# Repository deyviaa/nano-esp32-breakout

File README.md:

# 🛠️ ArdNanoESP32 DevBoard

> *A compact, feature-packed carrier board for the Arduino Nano ESP32 — bridging the gap between bare breadboard chaos and a polished development kit.*

---

## 📖 Overview

This project is a custom-designed **PCB carrier board** built around the **Arduino Nano ESP32** (dual-core Xtensa LX7, Wi-Fi + BLE). Sized to an approximate **iPhone footprint**, the board is designed as an intermediate prototyping platform with a philosophy of **hardware-level safety** ("student-proofing") — all peripherals are wired with protection resistors, clean logic states, and deliberate design choices baked in at the schematic level.

The board seats the Nano ESP32 in ZIF-style socket headers and exposes every GPIO to parallel jumper pin headers for external breadboard connectivity, while also integrating a full suite of on-board peripherals ready for immediate use.

**Current Status:**

```
✅ Schematic design — Complete & verified
✅ Component footprints — All assigned & resolved
✅ Git version control — Initialized (cross-platform)
🔄 PCB Layout & Routing — In Progress
⬜ Gerber Generation & Fab — Pending
⬜ Assembly & Bring-up — Pending
```

---

## ⚡ Power Architecture

The board runs two accessible power rails sourced from the Nano ESP32's onboard regulators:

| Rail | Source | Purpose |
|------|--------|---------|
| **5V** | `VUSB` | WS2812B LED, raw power header |
| **3.3V** | Nano onboard LDO | All logic peripherals, GPIO I/O, I2C bus |
| **GND** | Common ground | Shared reference for all rails |

All power rails are broken out to dedicated 4-pin headers on the board edge for external use.

---

## 🧩 Peripheral Map

```
┌─────────────────────────────────────────────────────────┐
│               Arduino Nano ESP32 Carrier Board           │
│                                                         │
│  ┌──────────────┐     ┌─────────────┐                   │
│  │ Nano ESP32   │     │  4x LEDs    │ ── 1kΩ CLR ── GPIO │
│  │  (socketed)  │     │  4x Buttons │ ── 10kΩ PD ── GPIO │
│  └──────────────┘     │  4x Switches│ ── 1kΩ SER ── GPIO │
│                        └─────────────┘                   │
│  ┌──────────────┐     ┌─────────────┐                   │
│  │  WS2812B     │     │  Qwiic/     │                   │
│  │  RGB LED     │     │  STEMMA QT  │ ── SDA(A4)/SCL(A5) │
│  │  (5V + 470Ω) │     │  JST-SH 4P  │ ── 4.7kΩ pull-ups  │
│  └──────────────┘     └─────────────┘                   │
│  ┌──────────────┐     ┌─────────────┐                   │
│  │  Alps RK09K  │     │  12mm Piezo │                   │
│  │  Rotary Pot  │     │  Buzzer     │ ── SW mute ── GPIO  │
│  │  (VDiv/A0)   │     │  (220Ω buf) │                   │
│  └──────────────┘     └─────────────┘                   │
└─────────────────────────────────────────────────────────┘
```

---

## 🔌 Peripheral Specifications

### 💡 LEDs × 4
- Generic standard LEDs, **active-high**
- **1kΩ** current-limiting resistors in series
- Clean GPIO drive, no floating states

### 🔘 Push Buttons × 4
- Momentary tactile switches
- **10kΩ pull-down** resistors → guaranteed `LOW` at rest
- No debounce hardware (handle in firmware or use `INPUT_PULLUP`)

### 🎚️ Slide Switches × 4 (Stateful GPIO Inputs)
- **SS12D00G-G3** SPDT Slide Switches (2.54mm pitch)
- Hard-wired: Pin 1 → 3.3V, Pin 3 → GND, Pin 2 → MCU
- **1kΩ series resistor** between common and GPIO — prevents a dead short if pin is accidentally configured as `OUTPUT LOW`
- ⚠️ *Avoid routing these to ESP32 strapping pins (GPIO0, GPIO3, GPIO45, GPIO46)*

### 🌈 WS2812B Addressable RGB LED
- **5050** form factor, driven from **VUSB (5V)** rail
- **100nF decoupling cap** placed physically adjacent to VDD/GND
- Data driven by 3.3V GPIO through **470Ω series resistor** (signal protection + level tolerance)
- `DOUT` left unconnected — ready for future LED chain expansion

### 🔁 Qwiic / STEMMA QT Connector (I2C)
- **JST-SH SM04B-SRSS-TB**, 1.0mm pitch, 4-pin
- Industry-standard pinout: `GND | 3V3 | SDA | SCL`
- Routed to hardware I2C: **SDA → A4**, **SCL → A5**
- **Two 4.7kΩ pull-up resistors** on SDA and SCL to 3.3V (open-drain compliant)
- Compatible with the entire Sparkfun/Adafruit Qwiic/STEMMA QT ecosystem

### 🎛️ Rotary Potentiometer
- **Alps RK09K** 9mm single-gang
- Wired as a safe voltage divider: Pin 1 → 3.3V, Pin 3 → GND, Wiper → Analog GPIO (A0–A7)
- Footprint includes 2 mechanical snap-in anchor pads for PCB stability

### 🔊 Piezo Buzzer
- **12mm PCB-mount** piezo, standard 7.62mm through-hole pitch
- **220Ω buffer resistor** on signal line
- **Hardware mute switch** (SS12D00 SPDT): one throw connects signal → buzzer positive; mute position leaves the throw floating (no drain-to-GND waste)

---

## 🗂️ Schematic Hierarchy

The project uses a hierarchical schematic structure in KiCad (4 sheets):

| Sheet | File | Contents |
|-------|------|----------|
| `/` | `ArdNanoESP32_DevBoard.kicad_sch` | Top-level hierarchy |
| `/MCU_Pins_Sockets/` | `MCU_Pins_Sockets.kicad_sch` | Nano ESP32 socket + jumper headers |
| `/PowerRails/` | `PowerRails.kicad_sch` | VUSB, 3V3, GND breakout headers |
| `/Peripherals/` | `Peripherals.kicad_sch` | All on-board peripherals |

---

## 🔧 KiCad Footprint Notes & Resolutions

Several non-obvious footprint decisions were made to match real-world, off-the-shelf components:

| Component | Footprint Assigned | Reason |
|---|---|---|
| SS12D00G-G3 Switches | `PinHeader_1x03_P2.54mm_Vertical` | Amazon-sourced units have **2.54mm pitch** (not standard 2mm) |
| Slide Switch Symbol | Generic `SW_SPDT` | Replaced Wuerth proprietary symbol — Pin 2 must be common to prevent 3V3↔GND short |
| JST-SH I2C Connector | `JST_SH_SM04B-SRSS-TB_1x04-1MP_P1.00mm_Horizontal` | Standard Qwiic/STEMMA 1.0mm pitch |
| Piezo Buzzer | `Buzzer_12x9.5mm_CR2032_Vertical` | Matches 7.62mm THT pin spacing |
| Alps Potentiometer | `Potentiometer_Alps_RK09K_Single_Vertical` | 3 signal pins + 2 mechanical anchor pads |
| Resistors (THT) | `R_Axial_DIN0207_L6.3mm_D2.5mm_P10.16mm_Horizontal` | Matches physical inventory |
| Resistors (SMD) | `R_0603_1608Metric_Pad1.05x0.95mm_HandSolder` | Hand-solder pad relief |

---

## 🌿 Git Workflow & Version Control

The repo is structured for **cross-platform KiCad development** (Windows PC ↔ MacBook Air).

### `.gitignore` covers:
```
# KiCad auto-generated / user-specific files
*.kicad_prl        # Per-user UI layout state
fp-info-cache      # Local footprint cache (rebuilt automatically)
*-bak              # KiCad backup files
*.lck              # Lock files (open-file indicators)
*_autosave-*       # Crash recovery autosaves
```

### ⚠️ Critical Workflow Rule

KiCad `.kicad_sch` and `.kicad_pcb` files are **binary-adjacent** — they do not merge cleanly. Follow this loop **strictly**:

```
┌─────────────────────────────────────────────┐
│                                             │
│   1. git pull  ← ALWAYS before opening     │
│   2. Open KiCad & do work                  │
│   3. Close KiCad (flushes file writes)     │
│   4. git add / commit / push               │
│                                             │
│   ❌ Never leave files open across machines │
│   ❌ Never commit while KiCad is open       │
│                                             │
└─────────────────────────────────────────────┘
```

---

## 🧰 Tools & Software

| Tool | Version | Purpose |
|------|---------|---------|
| **KiCad** | 8.0.x | Schematic capture & PCB layout |
| **Git** | Any | Version control |
| **Arduino IDE / PlatformIO** | Latest | Firmware development |

---

## 📐 Design Constraints

- **Target Form Factor:** ~iPhone footprint (≈ 71mm × 150mm)
- **MCU:** Arduino Nano ESP32 (seated, not soldered)
- **Logic Level:** 3.3V throughout
- **Power Input:** USB via Nano ESP32 onboard USB-C

---

## 🚧 Roadmap

- [x] Schematic capture (all 4 sheets)
- [x] ERC pass — no errors
- [x] Footprint assignment & verification
- [x] Git repo initialization + `.gitignore`
- [ ] PCB layout — component placement
- [ ] PCB routing — all nets
- [ ] DRC pass — no errors
- [ ] 3D model review
- [ ] Gerber generation
- [ ] PCB fabrication (JLCPCB / PCBWay)
- [ ] Board bring-up & hardware testing
- [ ] Firmware examples / demo sketches

---

## 📄 License

*To be determined.*

---

> *Designed in KiCad. Iterated on breadboards. Built to survive students.*

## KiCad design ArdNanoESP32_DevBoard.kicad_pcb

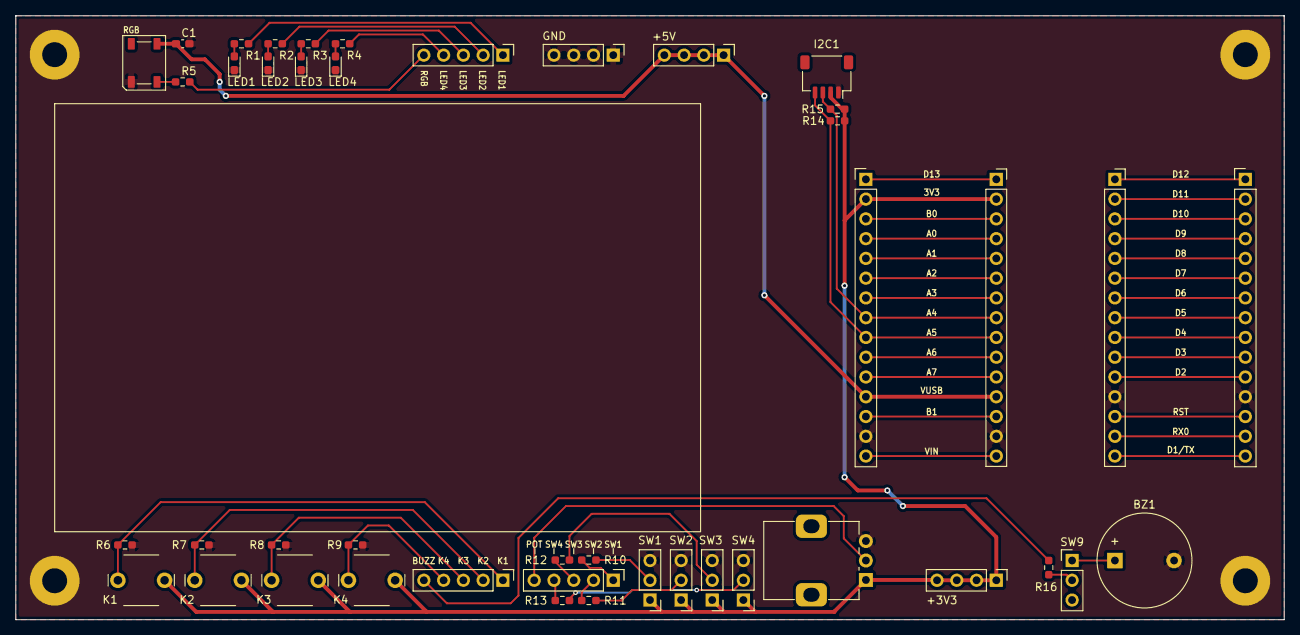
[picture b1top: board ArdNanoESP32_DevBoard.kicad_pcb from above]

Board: 2 copper layers, 163.0 x 77.6 mm, 44 parts (0 on the bottom side), 55 nets.

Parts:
+3V3, +5V: Conn_01x04; PinHeader_1x04_P2.54mm_Vertical
BZ1: Buzzer; Buzzer_12x9.5RM7.6
C1: 100n; C_0603_1608Metric_Pad1.08x0.95mm_HandSolder
D1: WS2812B; LED_WS2812B_PLCC4_5.0x5.0mm_P3.2mm
GND: Conn_01x04; PinHeader_1x04_P2.54mm_Vertical
I2C1: Conn_01x04_Socket; JST_SH_SM04B-SRSS-TB_1x04-1MP_P1.00mm_Horizontal
J1, J3: Conn_01x15_Pin; PinHeader_1x15_P2.54mm_Vertical
J2, J4: Conn_01x15_Socket; PinSocket_1x15_P2.54mm_Vertical
J8: Conn_01x05; PinHeader_1x05_P2.54mm_Vertical
K1, K2, K3, K4: SW_Push; SW_PUSH_6mm_H5mm_CUSTOM
LED1, LED2, LED3, LED4: LED; LED_0603_1608Metric_Pad1.05x0.95mm_HandSolder
LEDs1: Conn_01x05; PinHeader_1x05_P2.54mm_Vertical
R1, R2, R3, R4, R10, R11, R12, R13: 1k; R_0603_1608Metric_Pad0.98x0.95mm_HandSolder
R5: 470; R_0603_1608Metric_Pad0.98x0.95mm_HandSolder
R6, R7, R8, R9: 10k; R_0603_1608Metric_Pad0.98x0.95mm_HandSolder
R14, R15: 4.7k; R_0603_1608Metric_Pad0.98x0.95mm_HandSolder
R16: 220; R_0603_1608Metric_Pad0.98x0.95mm_HandSolder
RV1: R_Potentiometer_US; Potentiometer_Alps_RK09K_Single_Vertical
STATEFUL1: Conn_01x05; PinHeader_1x05_P2.54mm_Vertical
SW1, SW2, SW3, SW4, SW9: SW_SPDT; PinHeader_1x03_P2.54mm_Vertical

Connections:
3V3: +3V3.1, +3V3.2, +3V3.3, +3V3.4, I2C1.2, J1.2, J2.2, K1.1, K2.1, K3.1, K4.1, R14.2, R15.2, RV1.1, SW1.1 (A), SW2.1 (A), SW3.1 (A), SW4.1 (A)
/MCU_Pins_Sockets/A0: J1.4, J2.4
/MCU_Pins_Sockets/A1: J1.5, J2.5
/MCU_Pins_Sockets/A2: J1.6, J2.6
/MCU_Pins_Sockets/A3: J1.7, J2.7
/MCU_Pins_Sockets/A6: J1.10, J2.10
/MCU_Pins_Sockets/A7: J1.11, J2.11
/MCU_Pins_Sockets/B0: J1.3, J2.3
/MCU_Pins_Sockets/B1: J1.13, J2.13
/MCU_Pins_Sockets/D1/TX: J3.15, J4.15
/MCU_Pins_Sockets/D2: J3.11, J4.11
/MCU_Pins_Sockets/D3: J3.10, J4.10
/MCU_Pins_Sockets/D4: J3.9, J4.9
/MCU_Pins_Sockets/D5: J3.8, J4.8
/MCU_Pins_Sockets/D6: J3.7, J4.7
/MCU_Pins_Sockets/D7: J3.6, J4.6
/MCU_Pins_Sockets/D8: J3.5, J4.5
/MCU_Pins_Sockets/D9: J3.4, J4.4
/MCU_Pins_Sockets/D10: J3.3, J4.3
/MCU_Pins_Sockets/D11: J3.2, J4.2
/MCU_Pins_Sockets/D12: J3.1, J4.1
/MCU_Pins_Sockets/D13: J1.1, J2.1
/MCU_Pins_Sockets/RST: J3.13, J4.13
/MCU_Pins_Sockets/RX0: J3.14, J4.14
/MCU_Pins_Sockets/VIN: J1.15, J2.15
/Peripherals/BUZZ: J8.5, R16.1
/Peripherals/BUZZ_ANODE: BZ1.1 (+), SW9.1 (A)
/Peripherals/K1: J8.1, K1.2, R6.1
/Peripherals/K2: J8.2, K2.2, R7.1
/Peripherals/K3: J8.3, K3.2, R8.1
/Peripherals/K4: J8.4, K4.2, R9.1
/Peripherals/LED1: LEDs1.1, R1.1
/Peripherals/LED1_ANODE: LED1.2 (A), R1.2
/Peripherals/LED2: LEDs1.2, R2.1
/Peripherals/LED2_ANODE: LED2.2 (A), R2.2
/Peripherals/LED3: LEDs1.3, R3.1
/Peripherals/LED3_ANODE: LED3.2 (A), R3.2
/Peripherals/LED4: LEDs1.4, R4.1
/Peripherals/LED4_ANODE: LED4.2 (A), R4.2
/Peripherals/POT: RV1.2, STATEFUL1.5
/Peripherals/RGB: LEDs1.5, R5.1
/Peripherals/RGB_ANODE: D1.4 (DIN), R5.2
/Peripherals/ST1: R10.1, STATEFUL1.1
/Peripherals/ST2: R11.1, STATEFUL1.2
/Peripherals/ST3: R12.1, STATEFUL1.3
/Peripherals/ST4: R13.1, STATEFUL1.4
/Peripherals/SW1_COM: R10.2, SW1.2 (B)
/Peripherals/SW2_COM: R11.2, SW2.2 (B)
/Peripherals/SW3_COM: R12.2, SW3.2 (B)
/Peripherals/SW4_COM: R13.2, SW4.2 (B)
/Peripherals/SW9_COM: R16.2, SW9.2 (B)
A4: I2C1.3, J1.8, J2.8, R15.1
A5: I2C1.4, J1.9, J2.9, R14.1
GND: BZ1.2 (-), C1.2, D1.3 (VSS), GND.1, GND.2, GND.3, GND.4, I2C1.1, J1.14, J2.14, J3.12, J4.12, LED1.1 (K), LED2.1 (K), LED3.1 (K), LED4.1 (K), R6.2, R7.2, R8.2, R9.2, RV1.3, SW1.3 (C), SW2.3 (C), SW3.3 (C), SW4.3 (C)
VUSB: +5V.1, +5V.2, +5V.3, +5V.4, C1.1, D1.1 (VDD), J1.12, J2.12

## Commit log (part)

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2026-05-30 Schematic captures of different peripherals and pinouts
2026-05-30 New files to remove from tracking like history and macos stuff
2026-05-30 Markdown files featuring projet details and kicad shortcuts on macos for use with Claude AI
2026-05-30 - added global nets for A4 and A5
    - I2C connetor changes
    - Throw swtiches and button identifiers changed
2026-05-30 New custom Arduino Nano ESP32 outline footprint for guiding / dimension purposes
2026-05-30 PCB additions and placement of pinheaders and half-size breadboard
2026-05-30 New hotkey mods
2026-05-30 Project readme status as of 5/30
